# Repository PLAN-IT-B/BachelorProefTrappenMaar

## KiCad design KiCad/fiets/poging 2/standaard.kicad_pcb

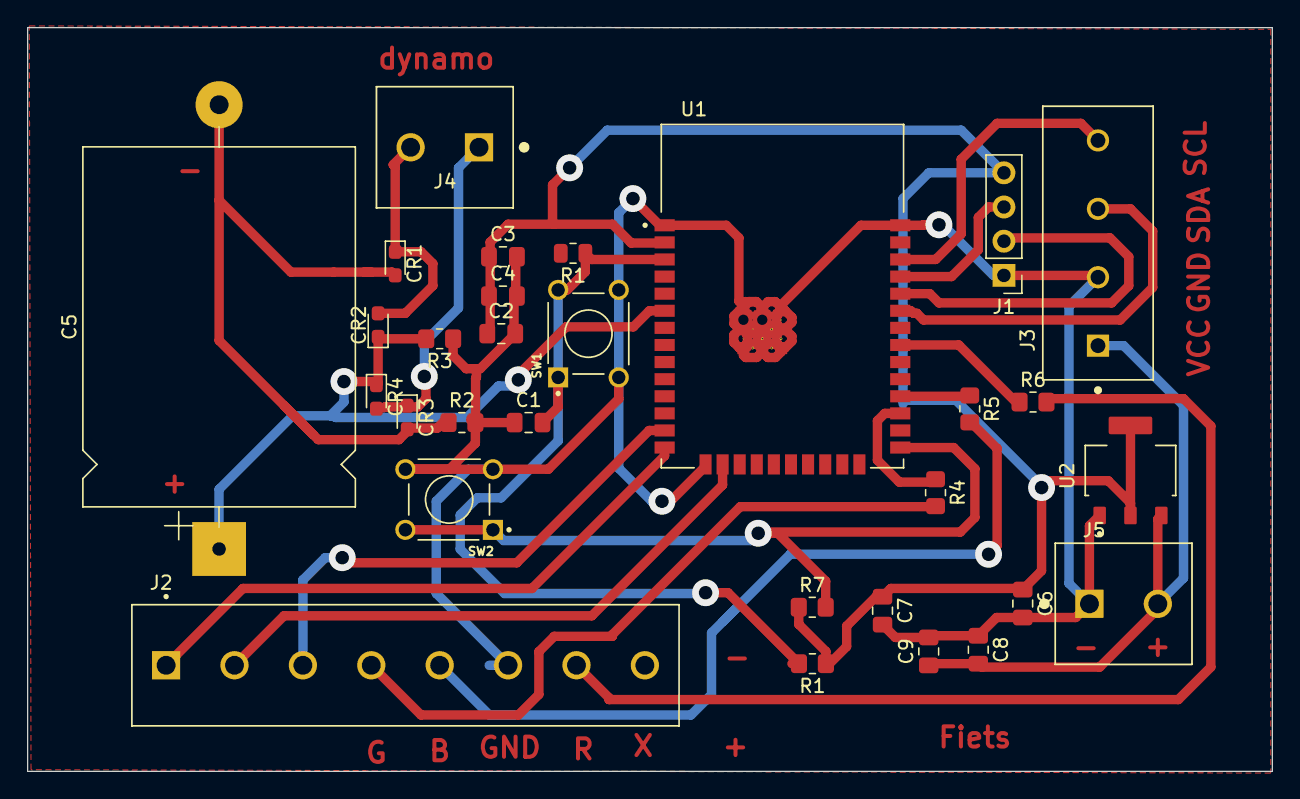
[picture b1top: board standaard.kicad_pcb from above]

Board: 2 copper layers, 92.5 x 55.2 mm, 30 parts (0 on the bottom side), 22 nets.

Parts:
C1: 1u; C_0805_2012Metric_Pad1.18x1.45mm_HandSolder
C2: 220u; C_0805_2012Metric_Pad1.18x1.45mm_HandSolder
C3: 22u; C_0805_2012Metric_Pad1.18x1.45mm_HandSolder
C4, C6, C8: 0.1u; C_0805_2012Metric_Pad1.18x1.45mm_HandSolder
C5: 1000µ; CP_Axial_L26.5mm_D20.0mm_P33.00mm_Horizontal
C7, C9: 4.7u; C_0805_2012Metric_Pad1.18x1.45mm_HandSolder
CR1, CR2, CR3, CR4: 1N4148W-TP; D_0603_1608Metric_Pad1.05x0.95mm_HandSolder
J1: Conn_01x04_Female; PinHeader_1x04_P2.54mm_Vertical
J2: R pinnen RGB strips; TE_282841-8
J3: 282837-4; TE_282837-4
J4, J5: 282841-2; TE_282841-2
R1: 10k; R_0805_2012Metric
R1#2, R7: 10k; R_0805_2012Metric_Pad1.20x1.40mm_HandSolder
R2: 560; R_0805_2012Metric_Pad1.20x1.40mm_HandSolder
R3: 120; R_0805_2012Metric_Pad1.20x1.40mm_HandSolder
R4, R5, R6: 82; R_0805_2012Metric_Pad1.20x1.40mm_HandSolder
SW1: ENABLE; SW_1825910-6-4
SW2: BOOT; SW_1825910-6-4
U1: ESP32-WROOM-32E_(16MB); XCVR_ESP32-WROOM-32E_(16MB)
U2: AMS1117; SOT229P700X180-4N

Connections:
5V: C8.2, C9.1, J3.1, J5.2, U2.3 (VIN)
+3V3: C2.1, C3.1, C4.1, C6.1, C7.1, J1.4, R1#2.1, R7.1, U1.2 (3V3), U2.2 (VOUT), U2.4 (VOUT)
GND: C1.1, C2.2, C3.2, C4.2, C6.2, C7.2, C8.1, C9.2, J1.1, J2.6, J3.2, J5.1, R2.2, R3.1, SW1.3, SW1.4, SW2.3, SW2.4, U1.1 (GND), U1.15 (GND), U1.38 (GND), U1.39_1 (GND), U1.39_2 (GND), U1.39_3 (GND), U1.39_4 (GND), U1.39_5 (GND), U1.39_6 (GND), U1.39_7 (GND), U1.39_8 (GND), U1.39_9 (GND), U2.1 (ADJ/GND)
unnamed: C1.2, R1.1, R1#2.2, SW1.1, SW1.2, U1.3 (EN)
unnamed: C5.1, CR2.1, CR4.1, R3.2, U1.6 (IO34)
unnamed: C5.2, CR1.2, CR3.2, R2.1
unnamed: CR1.1, CR2.2, J4.2
unnamed: CR3.1, CR4.2, J4.1
unnamed: J1.2, U1.34 (RXD0)
unnamed: J1.3, U1.35 (TXD0)
unnamed: J2.1, U1.14 (IO12)
unnamed: J2.2, U1.16 (IO13)
unnamed: J2.3, U1.13 (IO14)
unnamed: J2.4, R4.2
unnamed: J2.5, R5.2
unnamed: J2.7, R6.2
unnamed: J3.3, U1.33 (IO21)
unnamed: J3.4, U1.36 (IO22)
unnamed: R4.1, U1.27 (IO16)
unnamed: R5.1, U1.28 (IO17)
unnamed: R6.1, U1.31 (IO19)
unnamed: R7.2, SW2.1, SW2.2, U1.25 (IO0)

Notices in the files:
parts and their libraries:
COPYRIGHT: Copyright (C) 2018 Accelerated Designs. All rights reserved
